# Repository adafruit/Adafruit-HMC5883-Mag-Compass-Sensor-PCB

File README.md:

# Adafruit HMC5883 Magnetic Compass Sensor PCB (Discontinued)
<a href="http://www.adafruit.com/products/1746"><br/>
Click here to review the Adafruit shop</a>

We based this breakout on a popular and well loved magnetometer, the HMC5883L. This compact sensor uses I2C to communicate and its very easy to use. Since it's a 3.3V max chip, we added circuitry to make it 5V-safe logic and power, for easy use with either 3 or 5V microcontrollers. Simply connect VCC to +3-5V and ground to ground. Then read data from the I2C clock and data pins. There's also a Data Ready pin you can use to speed up reads.

PCB files for Adafruit HMC5883 Mag Compass Sensor PCB. The format is EagleCAD schematic and board layout
- https://www.adafruit.com/products/1746

### License

Adafruit invests time and resources providing this open source design, please support Adafruit and open-source hardware by purchasing products from [Adafruit](https://www.adafruit.com)!

All text above must be included in any redistribution

Designed by Limor Fried/Ladyada for Adafruit Industries.
Creative Commons Attribution/Share-Alike, all text above must be included in any redistribution. 
See license.txt for additional information.

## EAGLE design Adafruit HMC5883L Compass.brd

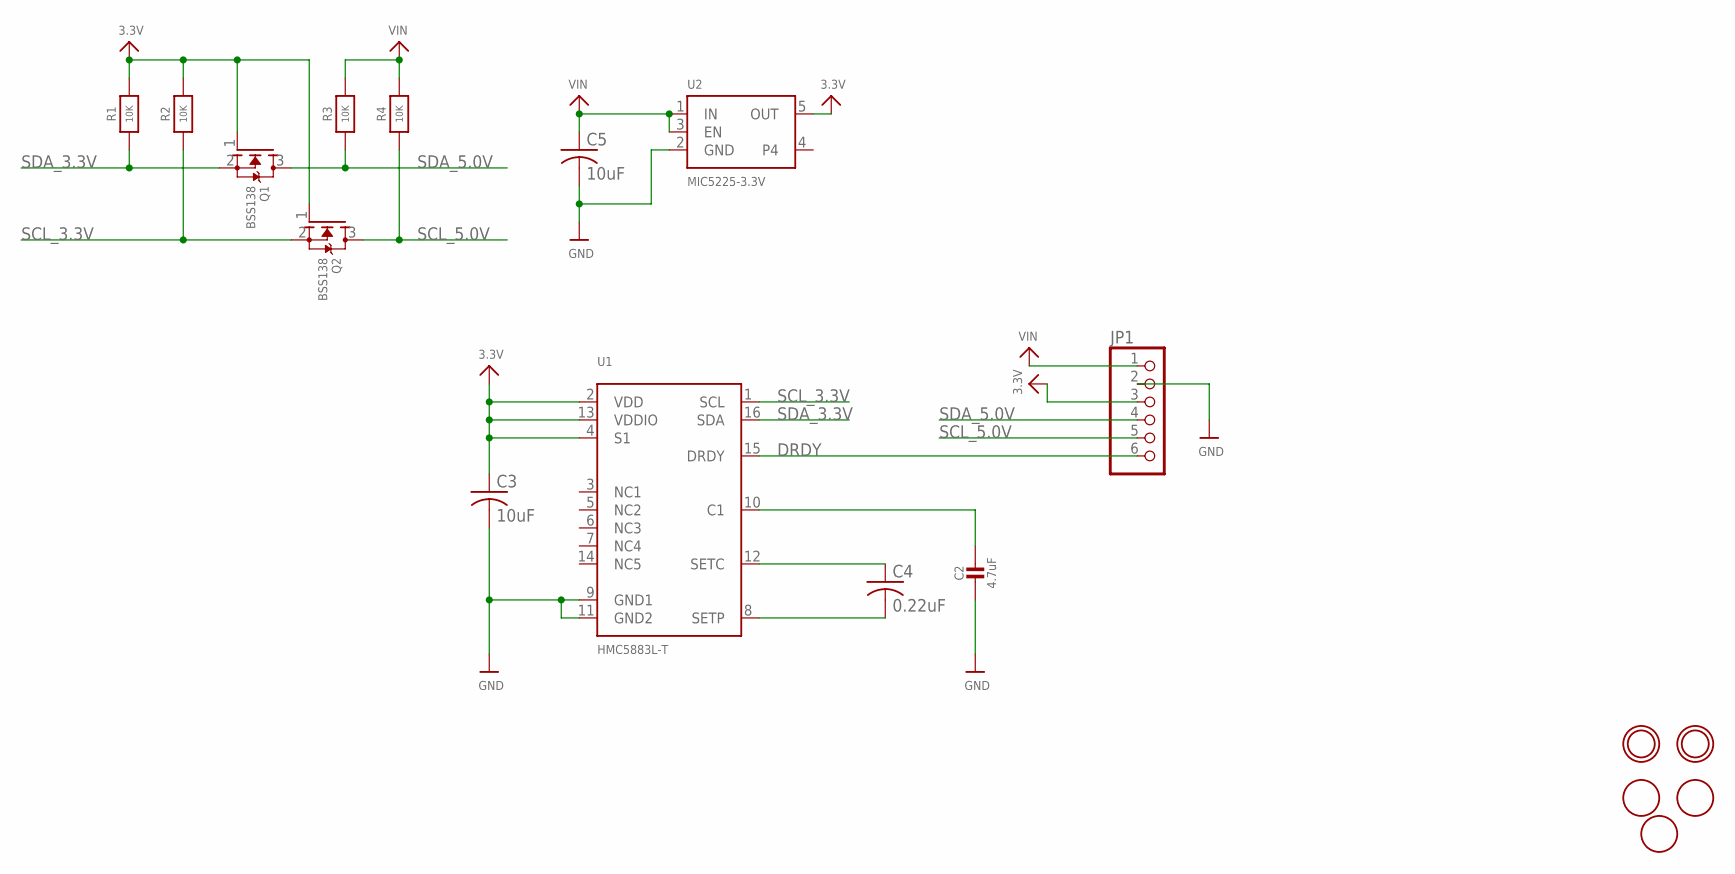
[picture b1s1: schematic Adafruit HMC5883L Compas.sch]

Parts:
C2: 4.7uF; 0805_10MGAP
C3, C5: 10uF; C0805
C4: 0.22uF; C0805
JP1: HEADER-1X676MIL; 1X06_ROUND_76
Q1, Q2: BSS138; SOT23-WIDE
R1, R2: 10K; _0805MP
R3, R4: 10K; 0805-NO
U1: HMC5883L-T; HMC5883L
U2: MIC5225-3.3V; SOT23-5
U$8, U$9: MOUNTINGHOLE2.5; MOUNTINGHOLE_2.5_PLATED
U$10, U$11, U$12: FIDUCIAL; FIDUCIAL_1MM

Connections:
3.3V: C3.1, JP1.3, Q1.1 (G), Q2.1 (G), R1.2, R2.2, U1.2 (VDD), U1.4 (S1), U1.13 (VDDIO), U2.5 (OUT)
DRDY: JP1.6, U1.15 (DRDY)
GND: C2.2, C3.2, C5.2, JP1.2, U1.9 (GND1), U1.11 (GND2), U2.2 (GND)
unnamed: C4.1, U1.12 (SETC)
unnamed: C4.2, U1.8 (SETP)
unnamed: C2.1, U1.10 (C1)
SCL_3.3V: Q2.2 (S), R2.1, U1.1 (SCL)
SCL_5.0V: JP1.5, Q2.3 (D), R4.1
SDA_3.3V: Q1.2 (S), R1.1, U1.16 (SDA)
SDA_5.0V: JP1.4, Q1.3 (D), R3.1
VIN: C5.1, JP1.1, R3.2, R4.2, U2.1 (IN), U2.3 (EN)

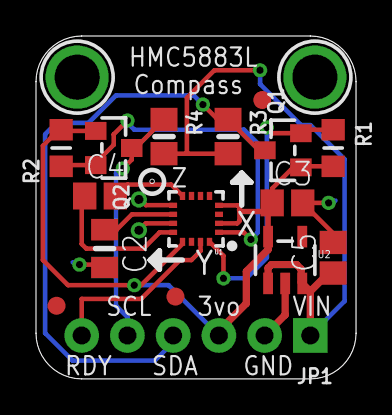
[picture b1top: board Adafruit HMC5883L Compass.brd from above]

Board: 2 copper layers, 17.8 x 19.1 mm, 19 parts (1 on the bottom side), 11 nets.

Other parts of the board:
U$7: ADAFRUIT_5MM

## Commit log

2015-04-16 init
